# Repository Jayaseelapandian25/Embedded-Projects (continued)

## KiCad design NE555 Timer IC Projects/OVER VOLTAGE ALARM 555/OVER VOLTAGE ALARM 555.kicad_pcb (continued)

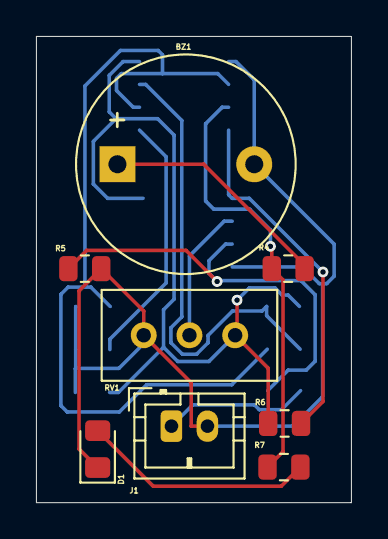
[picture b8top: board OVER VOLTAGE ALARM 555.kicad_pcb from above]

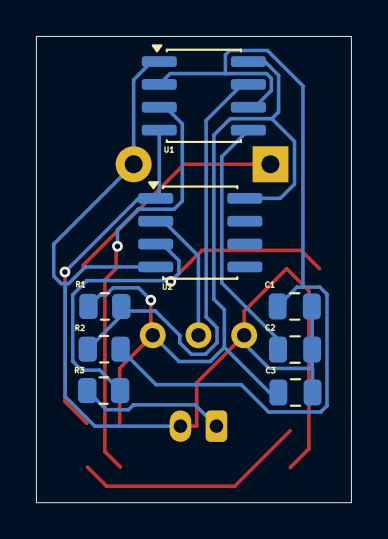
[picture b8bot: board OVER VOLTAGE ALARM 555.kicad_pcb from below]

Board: 2 copper layers, 17.5 x 25.9 mm, 16 parts (8 on the bottom side), 12 nets.
